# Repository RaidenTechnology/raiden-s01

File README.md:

# Raiden S0-1

**Open-hardware ESP32-S3 development board — designed from scratch in KiCad 9.**

## Overview

The Raiden S0-1 is a compact 4-layer devkit built around the **ESP32-S3FN8** (dual-core Xtensa LX7 @ 240 MHz, Wi-Fi + BLE 5, 8 MB embedded flash). Designed, routed and verified entirely by [Raiden Technology](https://github.com/RaidenTechnology).

| | |
|---|---|
| **MCU** | ESP32-S3FN8 (QFN-56, 8 MB flash) |
| **USB** | USB-C (USB 2.0), ESD-protected (PRTR5V0U2X), 5.1 kΩ CC pull-downs |
| **Power** | AZ1117C-3.3 LDO, 750 mA PTC resettable fuse, power LED |
| **RF** | U.FL (IPEX) antenna connector, feed line drawn for 50 Ω single-ended with a pi matching network — see the note below, impedance is **not** verified |
| **Clocks** | 40 MHz main crystal (CL = 8 pF) · 32.768 kHz RTC crystal (CL = 12.5 pF) |
| **I/O** | 2 × 15-pin 2.54 mm headers, BOOT + RESET buttons |
| **Board** | 4-layer FR-4, 1.6 mm — Sig / GND / +3V3 / Sig stackup, black soldermask |
| **Mounting** | 4 × M2 holes (NPTH) |

## Board views

| Top | Bottom |
|---|---|
|  |  |

## Verification

- **ERC: 0 errors** — **DRC: 0 errors, 0 unconnected items** (KiCad 9.0.7, `kicad-cli`)
- 5 permanent DRC notices are intentional local footprint overrides (U.FL RF keepout + M2 mounting holes)

### Known limitations

- **The RF feed is not impedance-verified.** The trace is drawn at 0.2 mm and the design intent is 50 Ω single-ended, but no controlled-impedance stackup was ever defined for the project, so 50 Ω is an assumption rather than a calculated or measured figure. The pi matching network (1 pF / 2.0 nH / 1 pF) uses starting values with no VNA behind them and is expected to be tuned after measurement.
- **The board has not been manufactured.** The design is complete and the fabrication package is generated, but no production run has happened, so nothing here has been validated on real silicon.

## Repository layout

```
hardware/   KiCad 9 project (schematic, PCB, project file)
fab/        Production package: Gerbers (4-layer), drill files,
            BOM + CPL (JLCPCB format), pick-and-place, schematic PDF
images/     kicad-cli 3D renders
```

## Fabrication notes

Full notes in [`fab/README.txt`](fab/README.txt). Highlights:

- Standard 4-layer stackup (JLC7628 or equivalent)
- RF feed line routed for 50 Ω single-ended — ask your fab to adjust trace width to their stackup
- Via-in-pad under the SOT-223 regulator tab: plugged (IPC-4761 Type VI) or at least tented
- QFN-56 (0.4 mm pitch) — stencil and reflow profile matter
- Crystal load capacitance is board-matched: use CL = 8 pF for the 40 MHz crystal (C9/C10 = 10 pF)

## Status

Rev A — design complete and verification-clean; first fabrication run pending.

## License

Hardware licensed under **CERN-OHL-P v2** ([LICENSE](LICENSE)). Use it, modify it, build on it.

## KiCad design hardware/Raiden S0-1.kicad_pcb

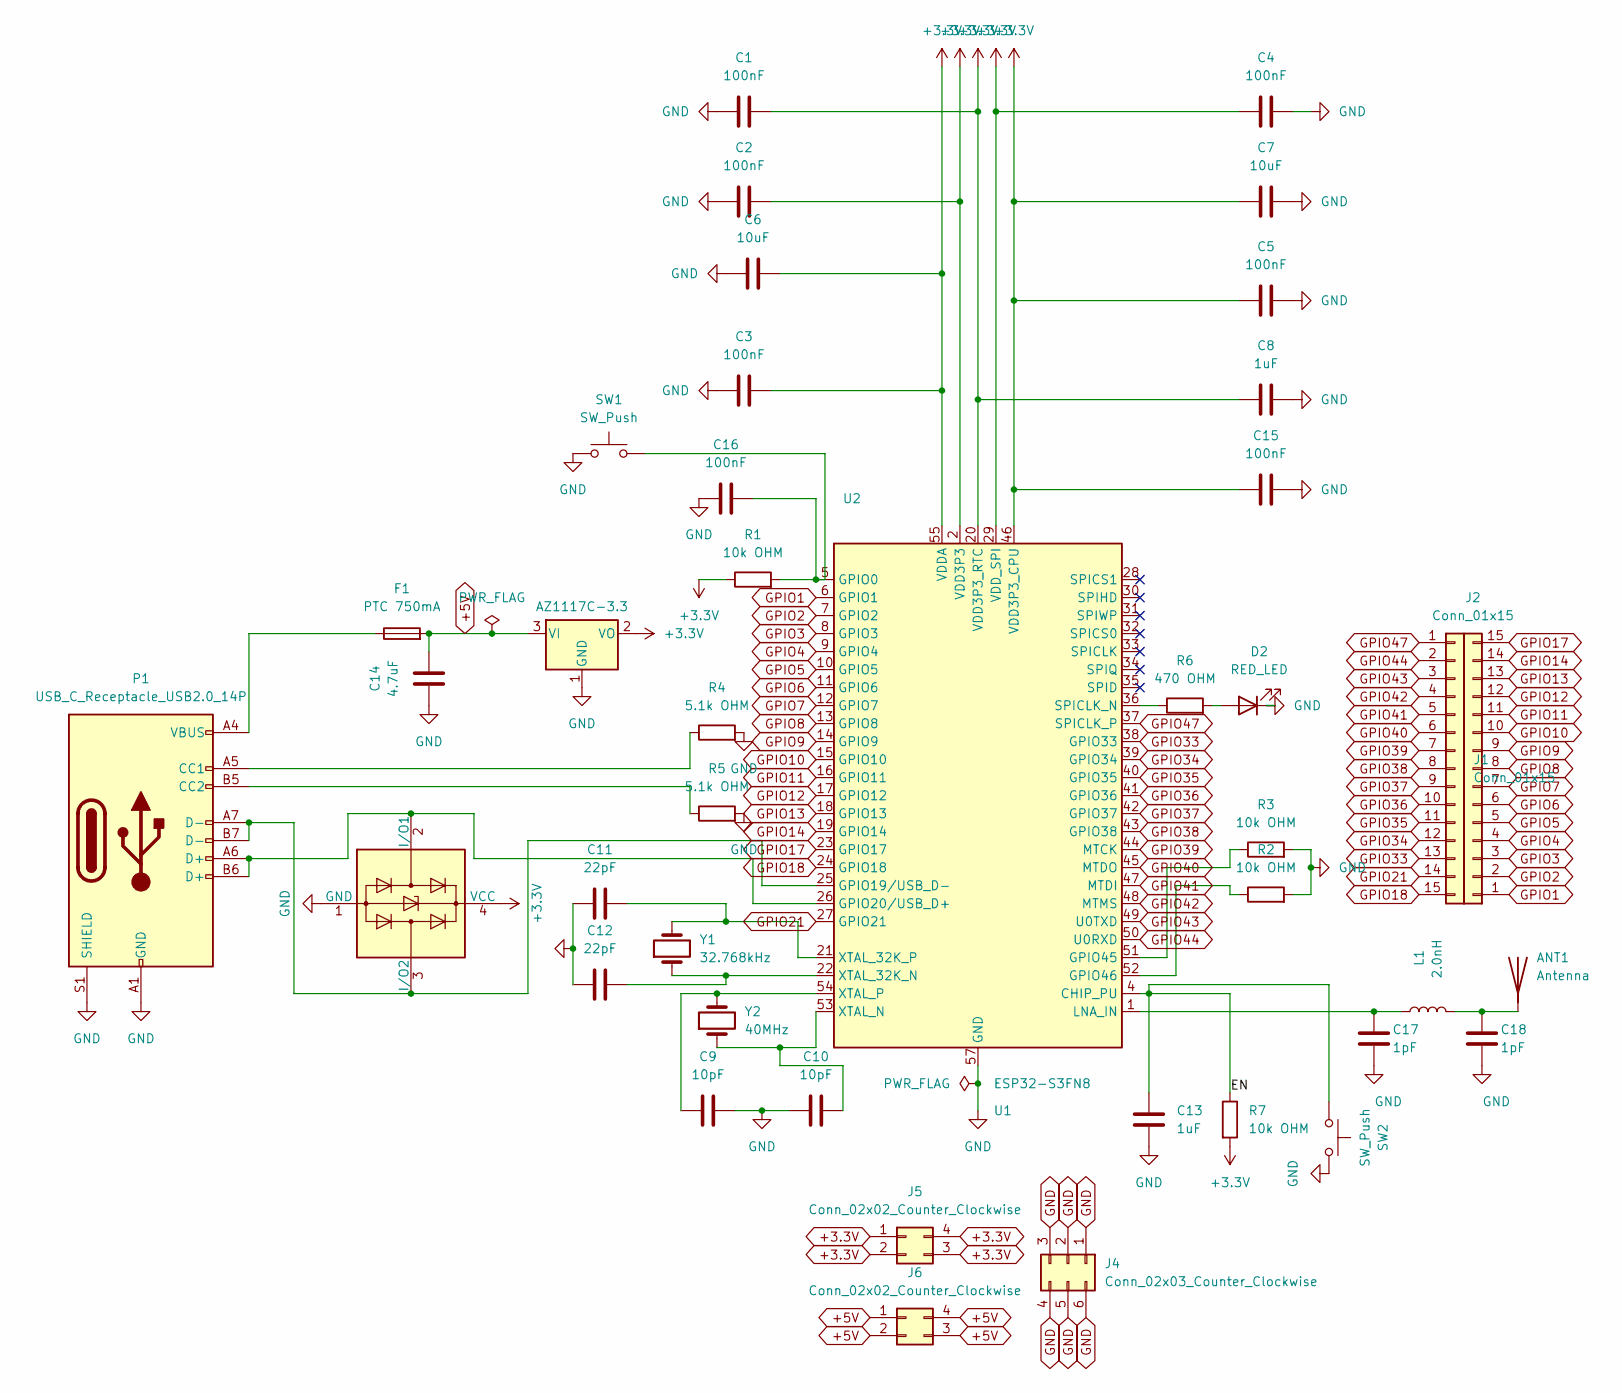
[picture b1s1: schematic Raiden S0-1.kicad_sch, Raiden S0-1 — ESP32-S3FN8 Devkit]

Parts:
ANT1: Antenna; U.FL_Hirose_U.FL-R-SMT-1_Vertical; MPN U.FL-R-SMT-1(10)
C1, C2, C3, C4, C5, C15, C16: 100nF; C_0603_1608Metric; MPN CL10B104KB8NNNC
C6, C7: 10uF; C_0603_1608Metric; MPN CL10A106KP8NNNC
C8, C13: 1uF; C_0603_1608Metric; MPN CL10A105KB8NNNC
C9, C10: 10pF; C_0603_1608Metric; MPN CL10C100JB8NNNC
C11, C12: 22pF; C_0603_1608Metric; MPN CL10C220JB8NNNC
C14: 4.7uF; C_0603_1608Metric; MPN CL10A475KP8NNNC
C17, C18: 1pF; C_0402_1005Metric; MPN CL05C010BB5NNNC
D1: PRTR5V0U2X; SOT-143; MPN PRTR5V0U2X,215
D2: RED_LED; LED_0603_1608Metric; MPN KT-0603R
F1: PTC 750mA; Fuse_1206_3216Metric; MPN 1206L075YR
J1, J2: Conn_01x15; PinHeader_1x15_P2.54mm_Vertical
J4: Conn_02x03_Counter_Clockwise; PinHeader_2x03_P2.54mm_Vertical
J5, J6: Conn_02x02_Counter_Clockwise; PinHeader_2x02_P2.54mm_Vertical
L1: 2.0nH; L_0402_1005Metric; MPN LQG15HS2N0S02D
P1: USB_C_Receptacle_USB2.0_14P; USB_C_Receptacle_HRO_TYPE-C-31-M-12; MPN TYPE-C-31-M-12
R1, R2, R3, R7: 10k OHM; R_0603_1608Metric; MPN 0603WAF1002T5E
R4, R5: 5.1k OHM; R_0603_1608Metric; MPN 0603WAF5101T5E
R6: 470 OHM; R_0603_1608Metric; MPN 0603WAF4700T5E
SW1, SW2: SW_Push; SW_SPST_B3S-1000; MPN B3S-1000
U1: ESP32-S3FN8; QFN-56-1EP_7x7mm_P0.4mm_EP4x4mm; MPN ESP32-S3FN8
U2: AZ1117C-3.3; SOT-223; MPN AZ1117CH-3.3TRG1
Y1: 32.768kHz; Crystal_SMD_3215-2Pin_3.2x1.5mm; MPN Q13FC1350000400
Y2: 40MHz; Crystal_SMD_5032-2Pin_5.0x3.2mm; MPN ECS-400-8-30B-CKM

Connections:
+3.3V: C1.2, C2.2, C3.2, C4.1, C5.1, C6.2, C7.1, C8.1, C15.1, D1.4 (VCC), J5.1, J5.2, J5.3, J5.4, R1.1, R7.2, U1.2 (VDD3P3), U1.3 (VDD3P3), U1.20 (VDD3P3_RTC), U1.29 (VDD_SPI), U1.46 (VDD3P3_CPU), U1.55 (VDDA), U1.56 (VDDA), U2.2 (VO), U2.4
+5V: C14.2, F1.2, J6.1, J6.2, J6.3, J6.4, U2.3 (VI)
/EN: C13.1, R7.1, SW2.1, U1.4 (CHIP_PU)
GND: ANT1.2, C1.1, C2.1, C3.1, C4.2, C5.2, C6.1, C7.2, C8.2, C9.1, C10.1, C11.1, C12.1, C13.2, C14.1, C15.2, C16.1, C17.2, C18.2, D1.1 (GND), D2.1 (K), J4.1, J4.2, J4.3, J4.4, J4.5, J4.6, P1.A1 (GND), P1.A12 (GND), P1.B1 (GND), P1.B12 (GND), P1.S1 (SHIELD), R2.2, R3.2, R4.2, R5.2, SW1.1, SW2.2, U1.57 (GND), U2.1 (GND)
GPIO1: J2.1, U1.6 (GPIO1)
GPIO2: J2.2, U1.7 (GPIO2)
GPIO3: J2.3, U1.8 (GPIO3)
GPIO4: J2.4, U1.9 (GPIO4)
GPIO5: J2.5, U1.10 (GPIO5)
GPIO6: J2.6, U1.11 (GPIO6)
GPIO7: J2.7, U1.12 (GPIO7)
GPIO8: J2.8, U1.13 (GPIO8)
GPIO9: J2.9, U1.14 (GPIO9)
GPIO10: J2.10, U1.15 (GPIO10)
GPIO11: J2.11, U1.16 (GPIO11)
GPIO12: J2.12, U1.17 (GPIO12)
GPIO13: J2.13, U1.18 (GPIO13)
GPIO14: J2.14, U1.19 (GPIO14)
GPIO17: J2.15, U1.23 (GPIO17)
GPIO18: J1.15, U1.24 (GPIO18)
GPIO21: J1.14, U1.27 (GPIO21)
GPIO33: J1.13, U1.38 (GPIO33)
GPIO34: J1.12, U1.39 (GPIO34)
GPIO35: J1.11, U1.40 (GPIO35)
GPIO36: J1.10, U1.41 (GPIO36)
GPIO37: J1.9, U1.42 (GPIO37)
GPIO38: J1.8, U1.43 (GPIO38)
GPIO39: J1.7, U1.44 (MTCK)
GPIO40: J1.6, U1.45 (MTDO)
GPIO41: J1.5, U1.47 (MTDI)
GPIO42: J1.4, U1.48 (MTMS)
GPIO43: J1.3, U1.49 (U0TXD)
GPIO44: J1.2, U1.50 (U0RXD)
GPIO47: J1.1, U1.37 (SPICLK_P)
unnamed: ANT1.1, C18.1, L1.2
unnamed: D1.2 (I/O1), P1.A6 (D+), P1.B6 (D+), U1.26 (GPIO20/USB_D+)
unnamed: D1.3 (I/O2), P1.A7 (D-), P1.B7 (D-), U1.25 (GPIO19/USB_D-)
unnamed: D2.2 (A), R6.2
unnamed: F1.1, P1.A4 (VBUS), P1.A9 (VBUS), P1.B4 (VBUS), P1.B9 (VBUS)
unnamed: P1.A5 (CC1), R4.1
unnamed: P1.B5 (CC2), R5.1
unnamed: C16.2, R1.2, SW1.2, U1.5 (GPIO0)
unnamed: R3.1, U1.51 (GPIO45)
unnamed: R2.1, U1.52 (GPIO46)
unnamed: C17.1, L1.1, U1.1 (LNA_IN)
unnamed: R6.1, U1.36 (SPICLK_N)
unnamed: C12.2, U1.22 (XTAL_32K_N), Y1.1
unnamed: C11.2, U1.21 (XTAL_32K_P), Y1.2
unnamed: C10.2, U1.53 (XTAL_N), Y2.1
unnamed: C9.2, U1.54 (XTAL_P), Y2.2

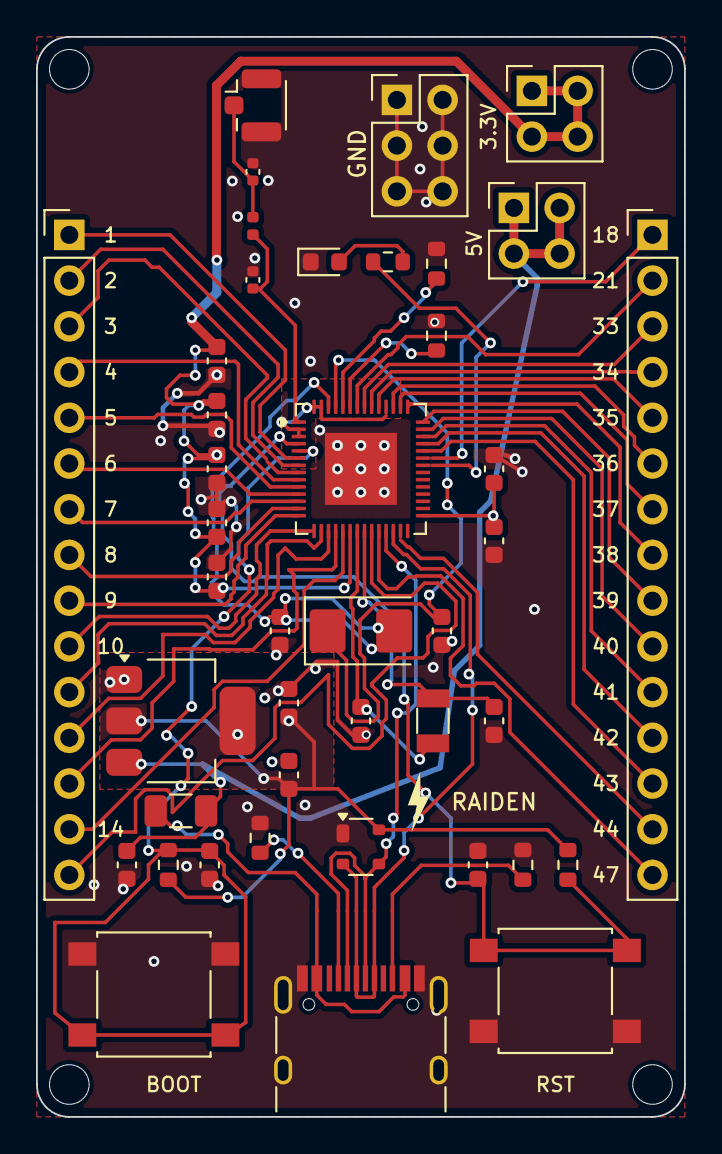
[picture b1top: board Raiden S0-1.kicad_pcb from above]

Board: 4 copper layers, 36.0 x 60.0 mm, 46 parts (0 on the bottom side), 50 nets.

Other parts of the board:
H1, H2, H3, H4: MountingHole_M2; MountingHole_2.2mm_M2

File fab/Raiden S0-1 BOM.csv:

"Reference","Value","MPN","Footprint"
"ANT1","Antenna","U.FL-R-SMT-1(10)","Connector_Coaxial:U.FL_Hirose_U.FL-R-SMT-1_Vertical"
"C1-C5,C15,C16","100nF","CL10B104KB8NNNC","Capacitor_SMD:C_0603_1608Metric"
"C6,C7","10uF","CL10A106KP8NNNC","Capacitor_SMD:C_0603_1608Metric"
"C8,C13","1uF","CL10A105KB8NNNC","Capacitor_SMD:C_0603_1608Metric"
"C9,C10","10pF","CL10C100JB8NNNC","Capacitor_SMD:C_0603_1608Metric"
"C11,C12","22pF","CL10C220JB8NNNC","Capacitor_SMD:C_0603_1608Metric"
"C14","4.7uF","CL10A475KP8NNNC","Capacitor_SMD:C_0603_1608Metric"
"C17,C18","1pF","CL05C010BB5NNNC","Capacitor_SMD:C_0402_1005Metric"
"D1","PRTR5V0U2X","PRTR5V0U2X,215","Package_TO_SOT_SMD:SOT-143"
"D2","RED_LED","KT-0603R","LED_SMD:LED_0603_1608Metric"
"F1","PTC 750mA","1206L075YR","Fuse:Fuse_1206_3216Metric"
"J1,J2","Conn_01x15","","Connector_PinHeader_2.54mm:PinHeader_1x15_P2.54mm_Vertical"
"J4","Conn_02x03_Counter_Clockwise","","Connector_PinHeader_2.54mm:PinHeader_2x03_P2.54mm_Vertical"
"J5,J6","Conn_02x02_Counter_Clockwise","","Connector_PinHeader_2.54mm:PinHeader_2x02_P2.54mm_Vertical"
"L1","2.0nH","LQG15HS2N0S02D","Inductor_SMD:L_0402_1005Metric"
"P1","USB_C_Receptacle_USB2.0_14P","TYPE-C-31-M-12","Connector_USB:USB_C_Receptacle_HRO_TYPE-C-31-M-12"
"R1-R3,R7","10k OHM","0603WAF1002T5E","Resistor_SMD:R_0603_1608Metric"
"R4,R5","5.1k OHM","0603WAF5101T5E","Resistor_SMD:R_0603_1608Metric"
"R6","470 OHM","0603WAF4700T5E","Resistor_SMD:R_0603_1608Metric"
"SW1,SW2","SW_Push","B3S-1000","Button_Switch_SMD:SW_SPST_B3S-1000"
"U1","ESP32-S3FN8","ESP32-S3FN8","Package_DFN_QFN:QFN-56-1EP_7x7mm_P0.4mm_EP4x4mm"
"U2","AZ1117C-3.3","AZ1117CH-3.3TRG1","Package_TO_SOT_SMD:SOT-223"
"Y1","32.768kHz","Q13FC1350000400","Crystal:Crystal_SMD_3215-2Pin_3.2x1.5mm"
"Y2","40MHz","ECS-400-8-30B-CKM","Crystal:Crystal_SMD_5032-2Pin_5.0x3.2mm"
